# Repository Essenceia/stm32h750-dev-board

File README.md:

# 10 year Anniversary developpement board

Minimal custom arm m7 devloppement board designed as a 10 year anniversary present. 

Selected MCU : STM32H750VBT6TR 

MCU package :  LQFP-100 

Requirements :

- SWD debug connected with pinout compatible with native 20 pin J-Link probe

- Route all remaining mcu pins to female connectors 

## Schematics

Schematic : [schematics](/doc/schematic.pdf)

## PCB

Resulting pcb, front : 

back :

## SWD - J-Link

SWD Connector Pinout:

The following table lists the J-Link / J-Trace SWD pinout.
|Pin|Signal|Type|Description|
|---|------|----|-----------|
|1|VTref|Input|This is the target reference voltage. It is used to check if the target has power, to create the logic-level reference for the input comparators and to control the output logic levels to the target. It is normally fed from Vdd of the target board and must not have a series resistor.|
|2|Vsupply|NC|This pin is not connected in J-Link. It is reserved for compatibility with other equipment. Connect to Vdd or leave open in target system.|
|3|Not used|NC|This pin is not used by J-Link. If the device may also be accessed via JTAG, this pin may be connected to nTRST, otherwise leave open.|
|5|Not used|NC|This pin is not used by J-Link. If the device may also be accessed via JTAG, this pin may be connected to TDI, otherwise leave open.|
|7|SWDIO|I/O|Single bi-directional data pin.|
|9|SWCLK|Output|Clock signal to target CPU. It is recommended that this pin is pulled to a defined state of the target board. Typically connected to TCK of target CPU.|
|11|Not used|NC|This pin is not used by J-Link. This pin is not used by J-Link when operating in SWD mode. If the device may also be accessed via JTAG, this pin may be connected to RTCK, otherwise leave open.|
|13|SWO|Input|Serial Wire Output trace port. (Optional, not required for SWD communication.)|
|15|nRESET|I/O|Target CPU reset signal. Typically connected to the RESET pin of the target CPU, which is typically called "nRST", "nRESET" or "RESET". This signal is an active low signal.|
|17|Not used|NC|This pin is not connected in J-Link.|
|19|5V-Supply|Output|This pin is used to supply power to some eval boards.|

Pins 4, 6, 8, 10, 12, 14, 16, 18, 20 are GND pins connected to GND in J-Link. They should also be connected to GND in the target system.

## Future improvements ideas

- After adding support for USB 3.0 and up switch usb b mini for thunderbolt

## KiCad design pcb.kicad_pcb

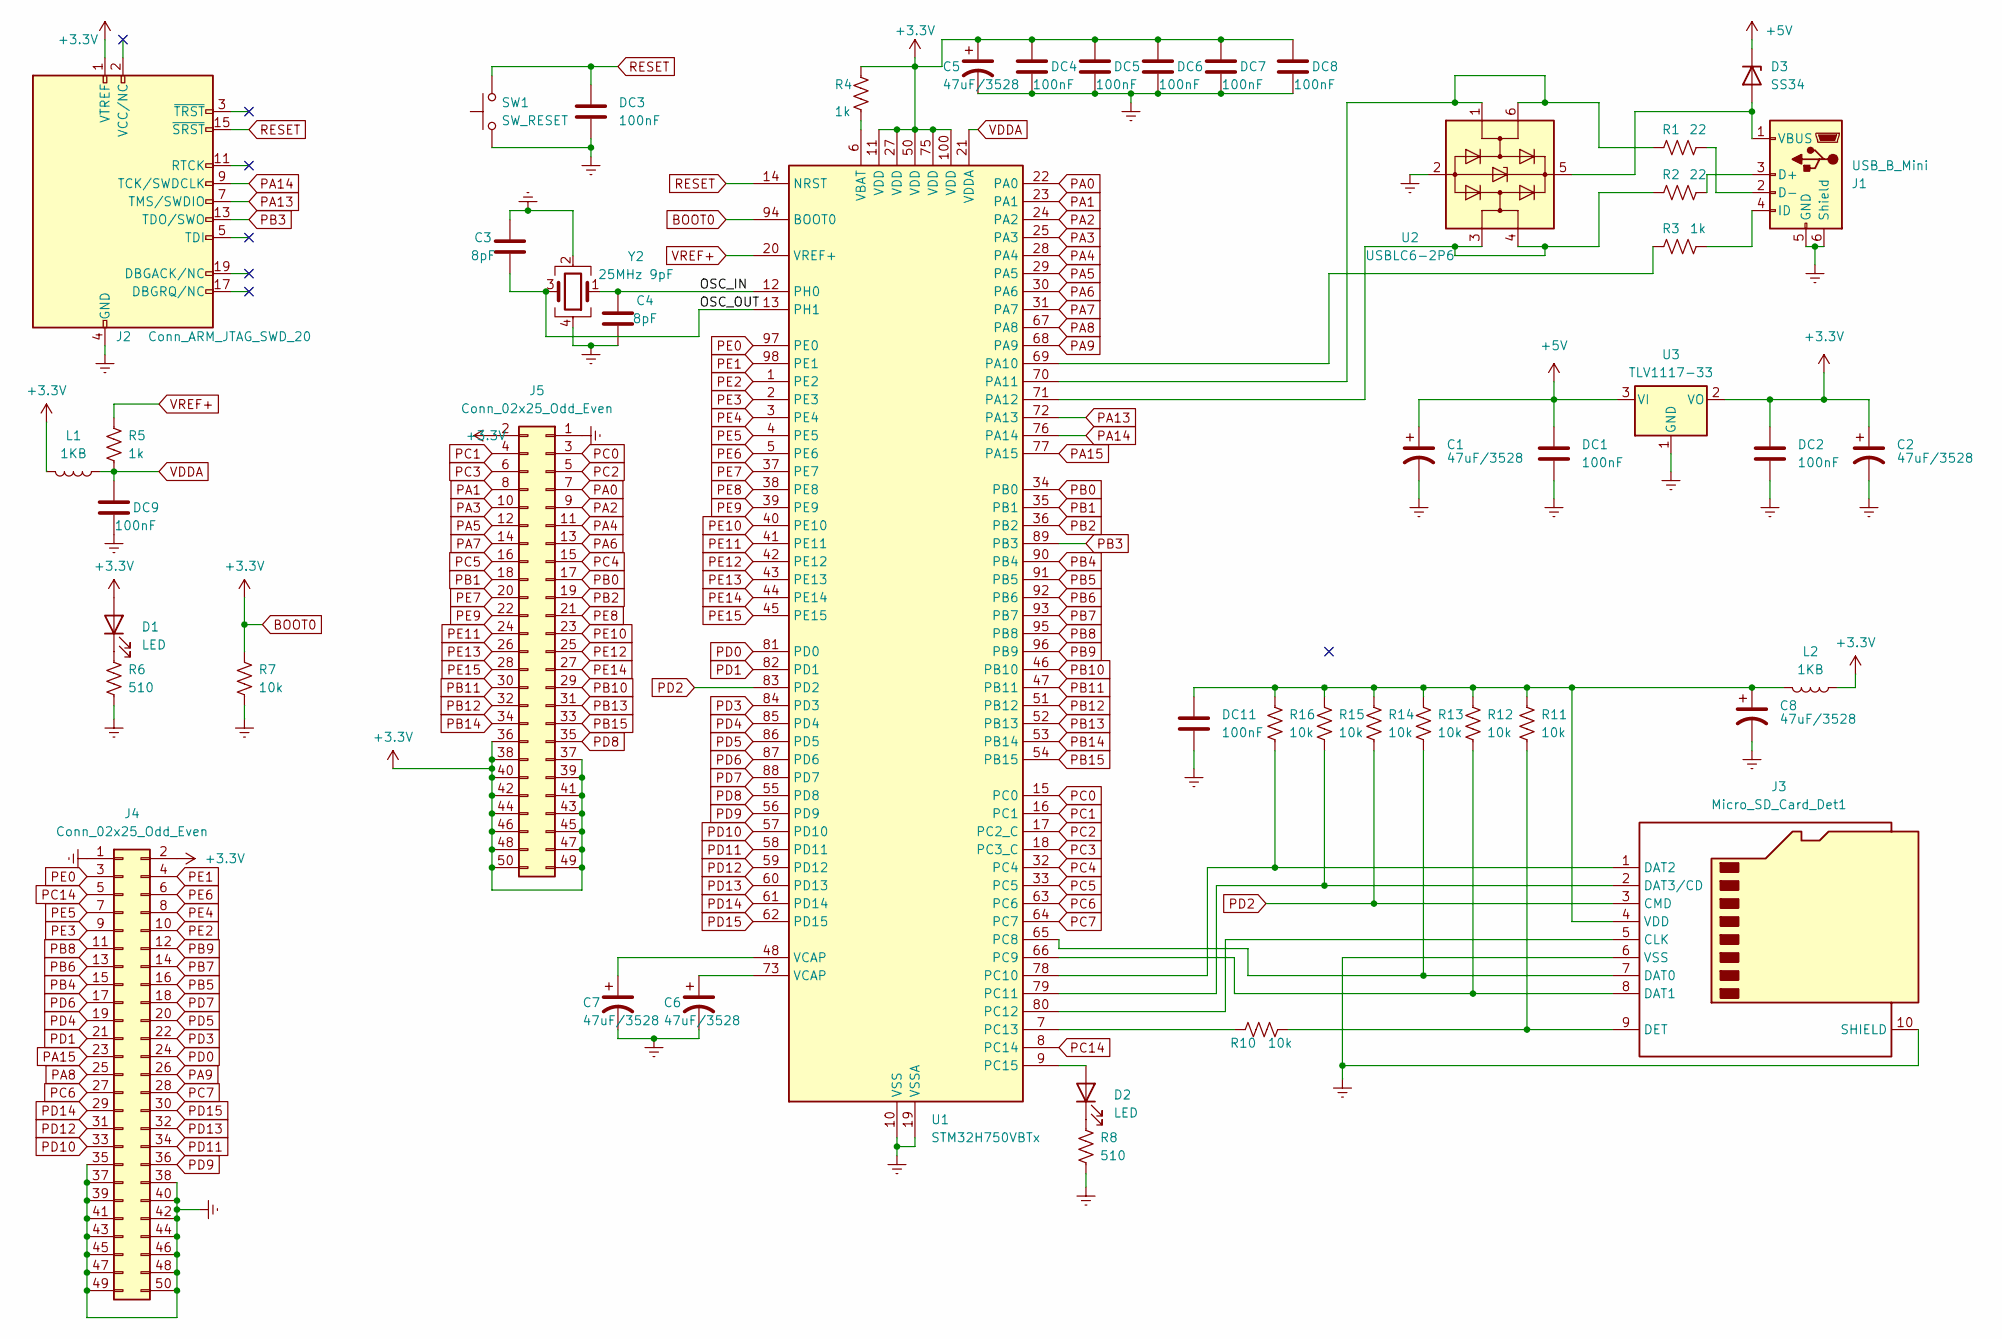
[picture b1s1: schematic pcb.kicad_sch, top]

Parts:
C1, C2, C5, C6, C7, C8: 47uF/3528; C_1206_3216Metric
C3, C4: 8pF; C_0402_1005Metric
D1, D2: LED; LED_0603_1608Metric
D3: SS34; D_SOD-123F
DC1, DC2, DC3, DC4, DC5, DC6, DC7, DC8, DC9, DC11: 100nF; C_0402_1005Metric
J1: USB_B_Mini; USB_Mini-B_Wuerth_65100516121_Horizontal
J2: Conn_ARM_JTAG_SWD_20; PinSocket_2x10_P2.54mm_Vertical
J3: Micro_SD_Card_Det1; microSD_HC_Molex_104031-0811
J4, J5: Conn_02x25_Odd_Even; PinSocket_2x25_P2.54mm_Vertical
L1, L2: 1KB; L_0603_1608Metric
R1, R2: 22; R_0402_1005Metric
R3, R4, R5: 1k; R_0603_1608Metric
R6, R8: 510; R_0603_1608Metric
R7, R10, R11, R12, R13, R14, R15, R16: 10k; R_0402_1005Metric
SW1: SW_RESET; SW_Tactile_SPST_NO_Straight_CK_PTS636Sx25SMTRLFS
U1: STM32H750VBTx; LQFP-100_14x14mm_P0.5mm
U2: USBLC6-2P6; SOT-666
U3: TLV1117-33; SOT-223
Y2: 25MHz 9pF; Crystal_SMD_2016-4Pin_2.0x1.6mm

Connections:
+5V: C1.1, D3.1 (K), DC1.1, U3.3 (VI)
/OSC_IN: C4.1, U1.12 (PH0), Y2.1
/OSC_OUT: C3.2, U1.13 (PH1), Y2.3
BOOT0: C2.1, C5.1, D1.2 (A), DC2.1, DC4.1, DC5.1, DC6.1, DC7.1, DC8.1, J2.1 (VTREF), J4.2, J5.2, J5.36, J5.37, J5.38, J5.39, J5.40, J5.41, J5.42, J5.43, J5.44, J5.45, J5.46, J5.47, J5.48, J5.49, J5.50, L1.2, L2.2, R4.1, R7.1, U1.11 (VDD), U1.27 (VDD), U1.50 (VDD), U1.75 (VDD), U1.94 (BOOT0), U1.100 (VDD), U3.2 (VO)
Earth: C1.2, C2.2, C3.1, C4.2, C5.2, C6.2, C7.2, C8.2, DC1.2, DC2.2, DC3.2, DC4.2, DC5.2, DC6.2, DC7.2, DC8.2, DC9.2, DC11.2, J1.5 (GND), J1.6 (Shield), J2.4 (GND), J2.6 (GND), J2.8 (GND), J2.10 (GND), J2.12 (GND), J2.14 (GND), J2.16 (GND), J2.18 (GND), J2.20 (GND), J3.6 (VSS), J3.10 (SHIELD), J4.1, J4.35, J4.37, J4.38, J4.39, J4.40, J4.41, J4.42, J4.43, J4.44, J4.45, J4.46, J4.47, J4.48, J4.49, J4.50, J5.1, R6.2, R7.2, R8.2, SW1.1, U1.10 (VSS), U1.19 (VSSA), U1.26 (VSS), U1.49 (VSS), U1.74 (VSS), U1.99 (VSS), U2.2 (GND), U3.1 (GND), Y2.2, Y2.4
unnamed: C6.1, U1.73 (VCAP)
unnamed: C7.1, U1.48 (VCAP)
unnamed: D1.1 (K), R6.1
unnamed: D2.2 (A), U1.9 (PC15)
unnamed: D2.1 (K), R8.1
unnamed: D3.2 (A), J1.1 (VBUS), U2.5 (VBUS)
unnamed: J1.3 (D+), R2.2
unnamed: J1.2 (D-), R1.2
unnamed: J1.4 (ID), R3.2
unnamed: J3.5 (CLK), U1.80 (PC12)
unnamed: J3.7 (DAT0), R13.2, U1.65 (PC8)
unnamed: J3.8 (DAT1), R12.2, U1.66 (PC9)
unnamed: J3.1 (DAT2), R16.2, U1.78 (PC10)
unnamed: J3.2 (DAT3/CD), R15.2, U1.79 (PC11)
unnamed: J3.9 (DET), R10.2, R11.2
unnamed: C8.1, DC11.1, J3.4 (VDD), L2.1, R11.1, R12.1, R13.1, R14.1, R15.1, R16.1
unnamed: R3.1, U1.69 (PA10)
unnamed: R1.1, U1.70 (PA11), U2.1 (I/O1), U2.6 (I/O1)
unnamed: R2.1, U1.71 (PA12), U2.3 (I/O2), U2.4 (I/O2)
unnamed: R10.1, U1.7 (PC13)
unnamed: R4.2, U1.6 (VBAT)
PA0: J5.7, U1.22 (PA0)
PA1: J5.8, U1.23 (PA1)
PA2: J5.9, U1.24 (PA2)
PA3: J5.10, U1.25 (PA3)
PA4: J5.11, U1.28 (PA4)
PA5: J5.12, U1.29 (PA5)
PA6: J5.13, U1.30 (PA6)
PA7: J5.14, U1.31 (PA7)
PA8: J4.25, U1.67 (PA8)
PA9: J4.26, U1.68 (PA9)
PA13: J2.7 (TMS/SWDIO), U1.72 (PA13)
PA14: J2.9 (TCK/SWDCLK), U1.76 (PA14)
PA15: J4.23, U1.77 (PA15)
PB0: J5.17, U1.34 (PB0)
PB1: J5.18, U1.35 (PB1)
PB2: J5.19, U1.36 (PB2)
PB3: J2.13 (TDO/SWO), U1.89 (PB3)
PB4: J4.15, U1.90 (PB4)
PB5: J4.16, U1.91 (PB5)
PB6: J4.13, U1.92 (PB6)
PB7: J4.14, U1.93 (PB7)
PB8: J4.11, U1.95 (PB8)
PB9: J4.12, U1.96 (PB9)
PB10: J5.29, U1.46 (PB10)
PB11: J5.30, U1.47 (PB11)
PB12: J5.32, U1.51 (PB12)
PB13: J5.31, U1.52 (PB13)
PB14: J5.34, U1.53 (PB14)
PB15: J5.33, U1.54 (PB15)
PC0: J5.3, U1.15 (PC0)
PC1: J5.4, U1.16 (PC1)
PC2: J5.5, U1.17 (PC2_C)
PC3: J5.6, U1.18 (PC3_C)
PC4: J5.15, U1.32 (PC4)
PC5: J5.16, U1.33 (PC5)
PC6: J4.27, U1.63 (PC6)
PC7: J4.28, U1.64 (PC7)
PC14: J4.5, U1.8 (PC14)
PD0: J4.24, U1.81 (PD0)
PD1: J4.21, U1.82 (PD1)
PD2: J3.3 (CMD), R14.2, U1.83 (PD2)
PD3: J4.22, U1.84 (PD3)
PD4: J4.19, U1.85 (PD4)
PD5: J4.20, U1.86 (PD5)
PD6: J4.17, U1.87 (PD6)
PD7: J4.18, U1.88 (PD7)
PD8: J5.35, U1.55 (PD8)
PD9: J4.36, U1.56 (PD9)
PD10: J4.33, U1.57 (PD10)
PD11: J4.34, U1.58 (PD11)
PD12: J4.31, U1.59 (PD12)
PD13: J4.32, U1.60 (PD13)
PD14: J4.29, U1.61 (PD14)
PD15: J4.30, U1.62 (PD15)
PE0: J4.3, U1.97 (PE0)
PE1: J4.4, U1.98 (PE1)
PE2: J4.10, U1.1 (PE2)
PE3: J4.9, U1.2 (PE3)
PE4: J4.8, U1.3 (PE4)
PE5: J4.7, U1.4 (PE5)
PE6: J4.6, U1.5 (PE6)
PE7: J5.20, U1.37 (PE7)
PE8: J5.21, U1.38 (PE8)
PE9: J5.22, U1.39 (PE9)
PE10: J5.23, U1.40 (PE10)
PE11: J5.24, U1.41 (PE11)
PE12: J5.25, U1.42 (PE12)
PE13: J5.26, U1.43 (PE13)
PE14: J5.27, U1.44 (PE14)
PE15: J5.28, U1.45 (PE15)
RESET: DC3.1, J2.15 (~SRST), SW1.2, U1.14 (NRST)
VDDA: DC9.1, L1.1, R5.2, U1.21 (VDDA)
VREF+: R5.1, U1.20 (VREF+)

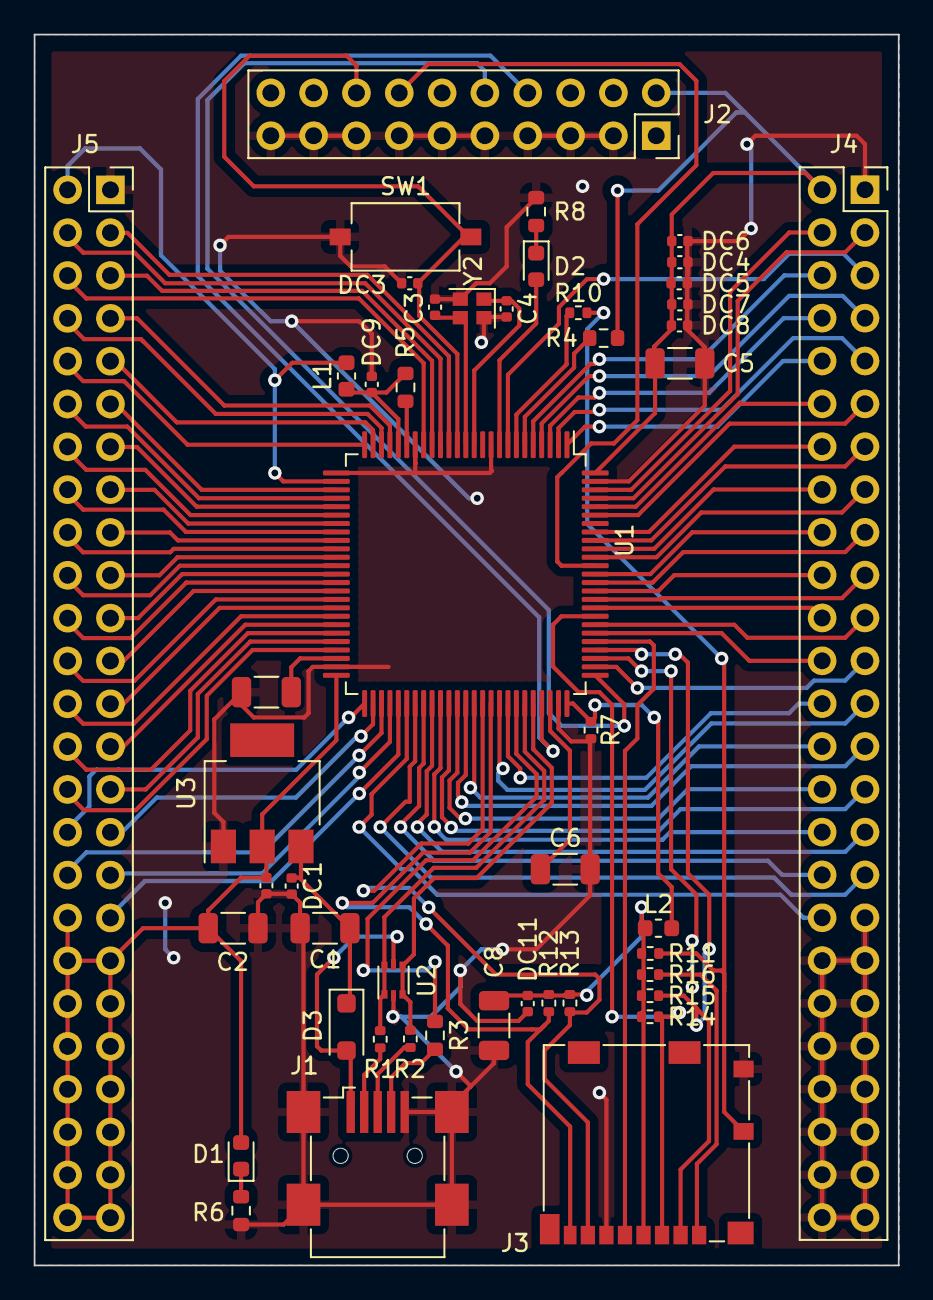
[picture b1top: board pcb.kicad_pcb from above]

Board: 2 copper layers, 51.2 x 73.0 mm, 48 parts (0 on the bottom side), 99 nets.

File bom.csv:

,,,,,,,,
,,,xxxx xxxx xxxxx xxPCS BOM  (Sample Bill of Materials),,,,,
,,,,,,,,
,,,,,,,,
,,,,,,,,
Item #,*Designator,*Qty,Manufacturer,*Mfg Part #,Description / Value,*Package/Footprint ,Type,Your Instructions / Notes
1,"DC6,DC3,DC5,DC4,DC8,DC9,DC7,DC11,DC1,DC2",10,KEMET,C0402C104K4RAC,100nF,0402,SMD,80-C0402C104K4RAC
2,U3,1,"
Texas Instruments                                            ",TLV1117-33CDCYRG3,TLV1117-33,SOT-223,SMD,595-TLV111733CDCYRG3
3,"R4,R5,R3",3,SEI Stackpole,RMCF0603JJ1K00,1k,0603,SMD,708-RMCF0603JJ1K00
4,Y2,1,ABRACON,ABM11-24.000MHz-9-B1U-T3,25MHz 9uF,2.0x1.6mm,SMD,815-1124000MHZ9B1UT3
5,"R15,R14,R13,R7,R16,R12,R10,R11",8,SEI Stackpole,RMCF01005JT10K0       ,10k,0402,SMD,708-RMCF01005JT10K0
6,U1,1,STMicroelectronics              ,STM32H750VBT6TR,STM32H750VBTx,LQFP-100,QFP,511-STM32H750VBT6TR
7,J2,1,On Shore Technology Inc.,302-S201,Conn_ARM_JTAG_SWD_20,THD,Through Hole,Digikey : ED10524-ND
8,"C8,C5,C6,C7,C1,C2",6,Murata Electronics,GRT31CC80J476KE13K,47uF/3528,1206,SMD,GRT31CC80J476KE13K
9,"D2,D1",2,EVERLIGHT,19-213SYGC/S530-E2/5T,LED,0603,SMD,
10,"R1,R2",2,SEI Stackpole,RMCF01005JT22R0,22,0402,SMD,708-RMCF01005JT22R0
11,"R6,R8",2,SEI Stackpole,RMCA0603JT510R,510,0603,SMD,708-RMCA0603JT510R
12,"C4,C3",2,Murata Electronics,GJM1555C1H8R0DB01D,8pF,0402,SMD,GJM1555C1H8R0DB01D
13,J3,1,Molex,1040310811,Micro_SD_Card_Det1,,SMD,Digikey  WM6357TR-ND
14,D3,1,Comchip Technology,SS34BF-HF,SS34,SOD-123,SMD,750-SS34BF-HF
15,"L1,L2",2,TAI-TECH,FCM 1608KF-102T02,1KB,0603,SMD,Digikey  4816-FCM1608KF-102T02TR-ND
16,SW1,1,C&K,RS282G05A3SMRT,SW_RESET,3.6x2.5mm,SMD,611-RS-282G05A3-SMRT
17,U2,1,STMicroelectronics,USBLC6-2P6,USBLC6-2P6,SOT-666,SMD,511-USBLC6-2P6
18,J1,1,TE Connectivity,1734035-5,USB_B_Mini,,SMD,571-1734035-5
19,"J4,J5",2,Oupiin,2044-2X25G00SA,Conn_02x25_Odd_Even,,Through Hole,Through Hole
,,,,,,,,
,,,,,,,,
,,,,,,,,
,,,,,,,,
,,,,,,,,
,,,,,,,,
,,,,,,,,
,,,,,,,,
Need a quick and accurante quote? Need an efficient production? Please read SMT Ordering Necessary Files & Info in 1 minute. Thank you very much!,,,,,,,,
,,,,,,,,
Click for Instructions on How to Create a BOM,,,,,,,,

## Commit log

2023-07-09 MCU: Selected target MCU stm32h750
2023-07-09 JLINK: Add jlink pinout for swd
2023-07-09 TODO: Add todolist
2023-07-10 KICAD: Update project files
2023-07-11 SCH: Update schematics, added everything appart from gpio pin header
2023-07-11 SCH: Schematic, no gpio connector
2023-07-12 SCH: Schematic mostly finished, missing pin connectors
2023-07-13 ROUTE: Routing finished, still needs to be re-worked but functionality is in place
2023-07-13 PCB: Routing finished, first version
2023-07-13 TODO: Update todo list
2023-07-14 PCB: Updated footprint of JTAG connector
2023-07-14 DOC: Update readme, added shematic pdf and frount/back coper layers
2023-07-14 DOC: Update pcb
2023-07-14 BOM: Added bill of material
2023-07-14 GBR: Added gebber and drill files
2023-07-14 BOM: Updates BOM to remove out of stock parts, switched out reset switch, new footprint SPST-NO 3.5x6.0mm, moved it away from connector due to it's higher profile
2023-07-14 PCB: Modified back silkscreen
2023-07-14 DOC: Update readme with note on this being an anniversary present
2023-07-14 DOC: Added 3d pcb view
2023-07-17 PCB: Fixed clearance violations
2023-07-22 ASSEMBLY: Added position file for pick and place
2023-08-17 DOC: Added picture of finished board, fount
2023-10-10 BOM: Updated bom, corrected item 5, 10 and 14 <- using wrong package, add mention of MCU for revision 2
2023-10-10 BOM: Correct footprint for item 14 sod-123 -> sod-123f
2023-10-10 BOM: Clean bom, line skip causing missalignement fixed
